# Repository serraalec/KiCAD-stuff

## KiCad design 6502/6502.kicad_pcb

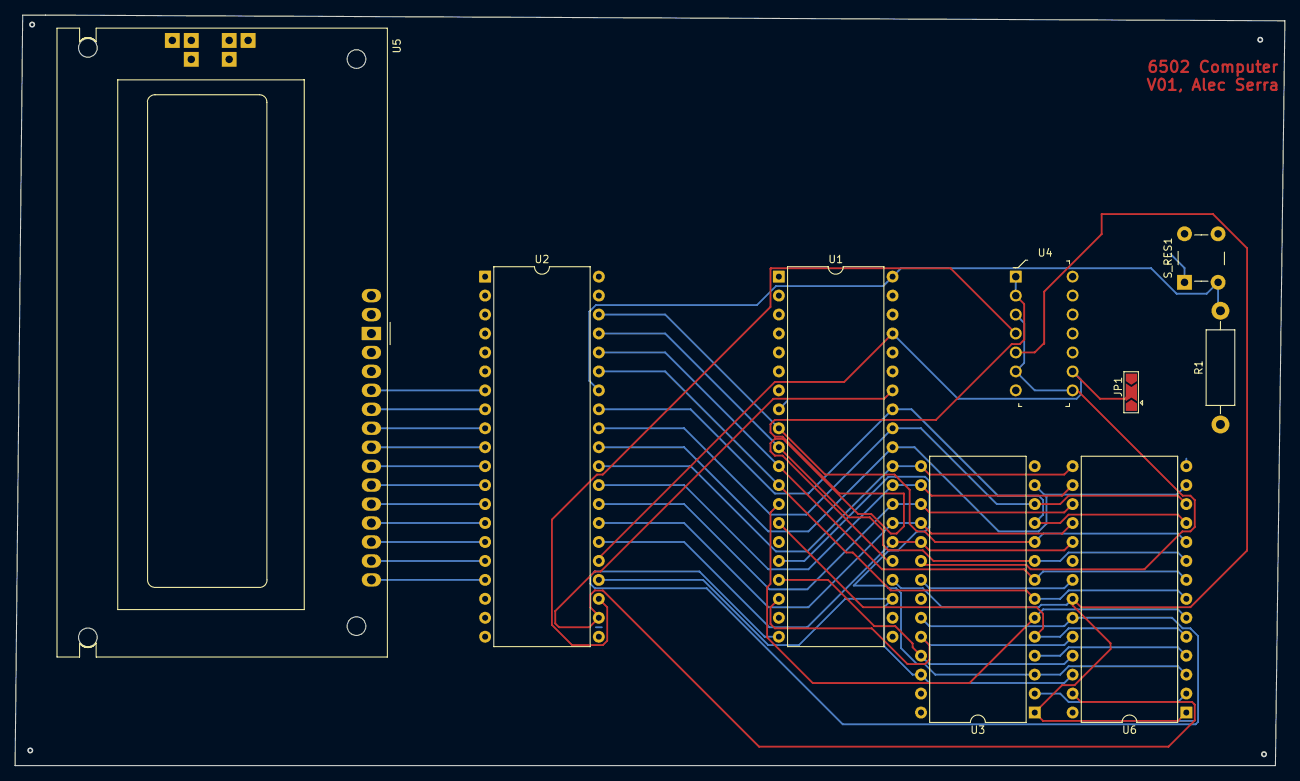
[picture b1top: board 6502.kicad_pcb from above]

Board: 4 copper layers, 170.2 x 100.6 mm, 9 parts (0 on the bottom side), 43 nets.

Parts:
JP1: SolderJumper_2_Bridged; SolderJumper-3_P2.0mm_Open_TrianglePad1.0x1.5mm
R1: 1kΩ; R_Axial_DIN0411_L9.9mm_D3.6mm_P15.24mm_Horizontal
S_RES1: B3F-1052; Switch_Tactile_THT_B3F-1xxx
U1: W65C02S; DIP-40_W15.24mm
U2: W65C22; DIP-40_W15.24mm
U3: at28c256; DIP-28_W15.24mm
U4: CD4093BE; DIP-14_W3mm
U5: RC1602A-GHW-ESX; RC1602A
U6: HM62256BLP; DIP-28_W15.24mm

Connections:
+5V: R1.1, U1.2, U1.4, U1.6, U1.8, U1.38, U2.20, U3.27, U3.28, U4.14, U5.2, U5.15, U6.14, U6.28
/A0: U1.9, U2.38, U3.10, U6.10
/A1: U1.10, U2.37, U3.9, U6.9
/A2: U1.11, U2.36, U3.8, U6.8
/A3: U1.12, U2.35, U3.7, U6.7
/A4: U1.13, U3.6, U6.6
/A5: U1.14, U3.5, U6.5
/A6: U1.15, U3.4, U6.4
/A7: U1.16, U3.3, U6.3
/A8: U1.17, U3.25, U6.25
/A9: U1.18, U3.24, U6.24
/A10: U1.19, U3.21, U6.21
/A11: U1.20, U3.23, U6.23
/A12: U1.22, U3.2, U6.2
/A13: U1.23, U2.24, U3.26, U6.26
/A14: U1.24, U3.1, U4.5, U6.1, U6.22
/A15: U1.25, U4.1, U4.2
/D0: U1.33, U2.33, U3.11, U6.11
/D1: U1.32, U2.32, U3.12, U6.12
/D2: U1.31, U2.31, U3.13, U6.13
/D3: U1.30, U2.30, U3.15, U6.15
/D4: U1.29, U2.29, U3.16, U6.16
/D5: U1.28, U2.28, U3.17, U6.17
/D6: U1.27, U2.27, U3.18, U6.18
/D7: U1.26, U2.26, U3.19, U6.19
/DA5: U2.7, U5.4
/DA6: U2.8, U5.5
/DA7: U2.9, U5.6
/DB0: U2.10, U5.7
/DB1: U2.11, U5.8
/DB2: U2.12, U5.9
/DB3: U2.13, U5.10
/DB4: U2.14, U5.11
/DB5: U2.15, U5.12
/DB6: U2.16, U5.13
/DB7: U2.17, U5.14
CLK: JP1.2, U1.37, U2.25, U4.9
EEPROM_EN: U3.20, U4.3, U4.6, U4.8
GND: S_RES1.1, U1.21, U2.1, U3.14, U3.22, U4.7, U5.1, U5.16
READ_WRITE: U1.34, U2.22, U6.27
RES: R1.2, S_RES1.3, U1.40, U2.34
~RAM_EN: U4.10, U6.20
~SELECT: U2.23, U4.4

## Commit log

2020-08-24 Add files via upload
    6502 symbol for kicad
